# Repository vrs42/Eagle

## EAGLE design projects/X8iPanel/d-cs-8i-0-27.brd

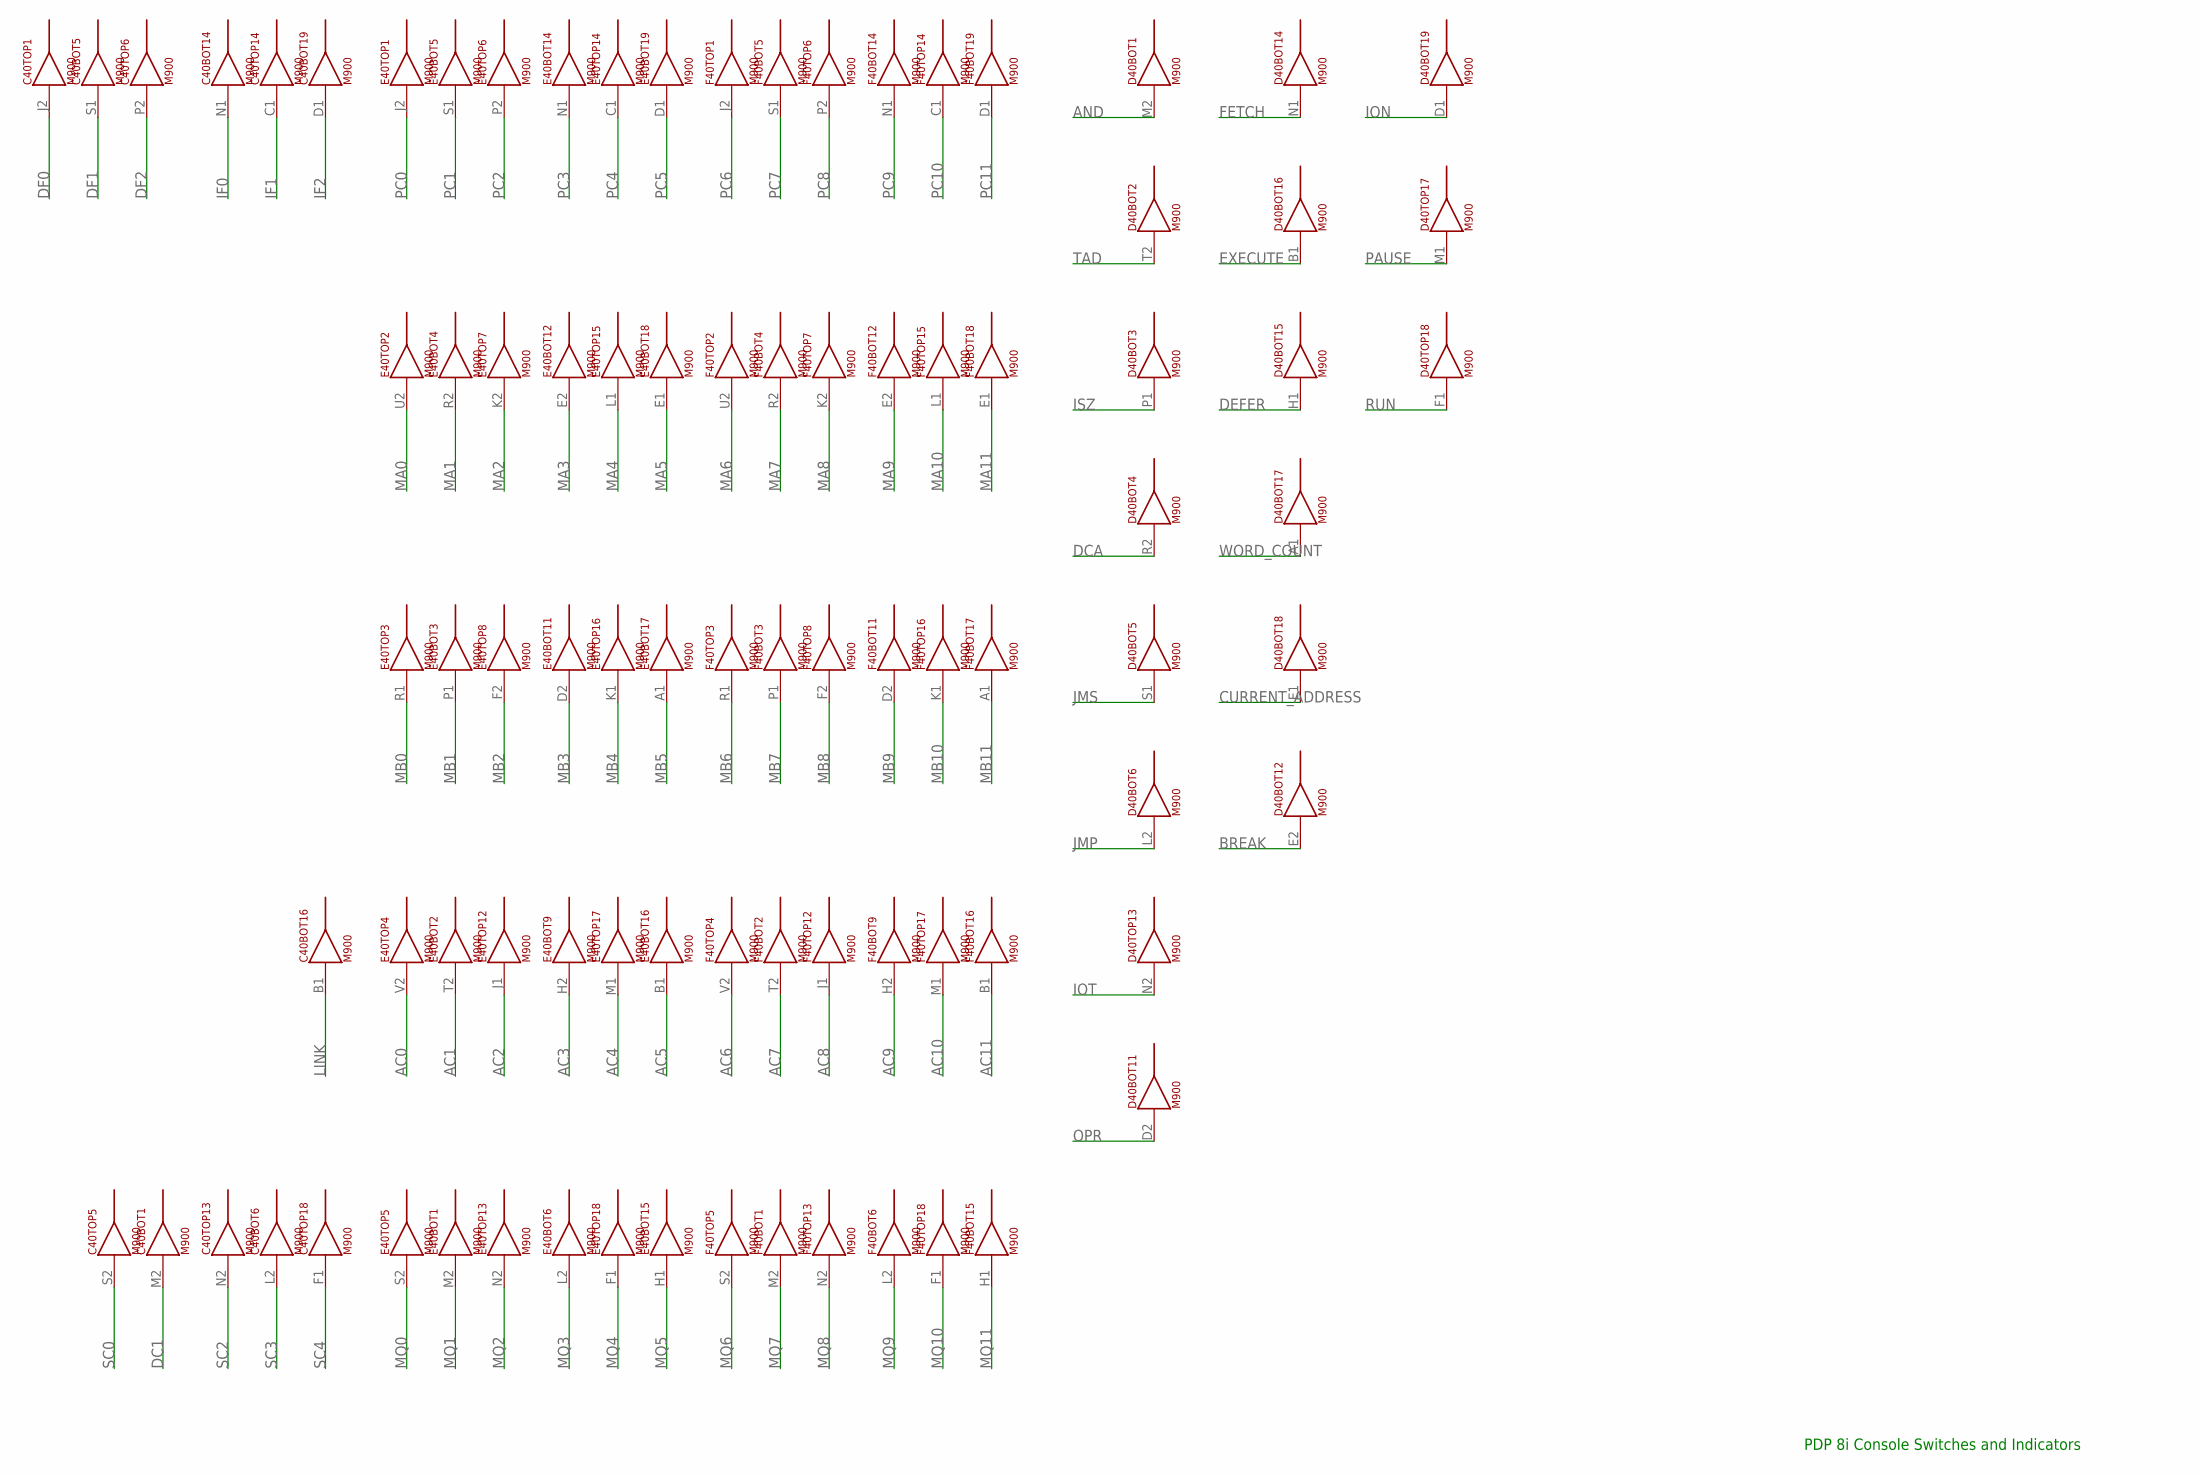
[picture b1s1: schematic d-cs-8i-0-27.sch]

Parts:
C40: M900; H807
D40: M900; H807
E40: M900; H807
F40: M900; H807

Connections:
AC0: E40.V2 (1)
AC1: E40.T2 (1)
AC2: E40.J1 (1)
AC3: E40.H2 (1)
AC4: E40.M1 (1)
AC5: E40.B1 (1)
AC6: F40.V2 (1)
AC7: F40.T2 (1)
AC8: F40.J1 (1)
AC9: F40.H2 (1)
AC10: F40.M1 (1)
AC11: F40.B1 (1)
AND: D40.M2 (1)
BREAK: D40.E2 (1)
CURRENT_ADDRESS: D40.E1 (1)
DC1: C40.M2 (1)
DCA: D40.R2 (1)
DEFER: D40.H1 (1)
DF0: C40.J2 (1)
DF1: C40.S1 (1)
DF2: C40.P2 (1)
EXECUTE: D40.B1 (1)
FETCH: D40.N1 (1)
GND: C40.C2 (GND), C40.T1 (GND), D40.C2 (GND), D40.T1 (GND), E40.C2 (GND), E40.T1 (GND), F40.C2 (GND), F40.T1 (GND)
IF0: C40.N1 (1)
IF1: C40.C1 (1)
IF2: C40.D1 (1)
ION: D40.D1 (1)
IOT: D40.N2 (1)
ISZ: D40.P1 (1)
JMP: D40.L2 (1)
JMS: D40.S1 (1)
LINK: C40.B1 (1)
MA0: E40.U2 (1)
MA1: E40.R2 (1)
MA2: E40.K2 (1)
MA3: E40.E2 (1)
MA4: E40.L1 (1)
MA5: E40.E1 (1)
MA6: F40.U2 (1)
MA7: F40.R2 (1)
MA8: F40.K2 (1)
MA9: F40.E2 (1)
MA10: F40.L1 (1)
MA11: F40.E1 (1)
MB0: E40.R1 (1)
MB1: E40.P1 (1)
MB2: E40.F2 (1)
MB3: E40.D2 (1)
MB4: E40.K1 (1)
MB5: E40.A1 (1)
MB6: F40.R1 (1)
MB7: F40.P1 (1)
MB8: F40.F2 (1)
MB9: F40.D2 (1)
MB10: F40.K1 (1)
MB11: F40.A1 (1)
MQ0: E40.S2 (1)
MQ1: E40.M2 (1)
MQ2: E40.N2 (1)
MQ3: E40.L2 (1)
MQ4: E40.F1 (1)
MQ5: E40.H1 (1)
MQ6: F40.S2 (1)
MQ7: F40.M2 (1)
MQ8: F40.N2 (1)
MQ9: F40.L2 (1)
MQ10: F40.F1 (1)
MQ11: F40.H1 (1)
OPR: D40.D2 (1)
PAUSE: D40.M1 (1)
PC0: E40.J2 (1)
PC1: E40.S1 (1)
PC2: E40.P2 (1)
PC3: E40.N1 (1)
PC4: E40.C1 (1)
PC5: E40.D1 (1)
PC6: F40.J2 (1)
PC7: F40.S1 (1)
PC8: F40.P2 (1)
PC9: F40.N1 (1)
PC10: F40.C1 (1)
PC11: F40.D1 (1)
RUN: D40.F1 (1)
SC0: C40.S2 (1)
SC2: C40.N2 (1)
SC3: C40.L2 (1)
SC4: C40.F1 (1)
TAD: D40.T2 (1)
VCC: C40.A2 (VCC), D40.A2 (VCC), E40.A2 (VCC), F40.A2 (VCC)
WORD_COUNT: D40.A1 (1)

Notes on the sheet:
PDP 8i Console Switches and Indicators

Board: 2 copper layers, 4 parts (0 on the bottom side), 2 nets, no tracks yet.

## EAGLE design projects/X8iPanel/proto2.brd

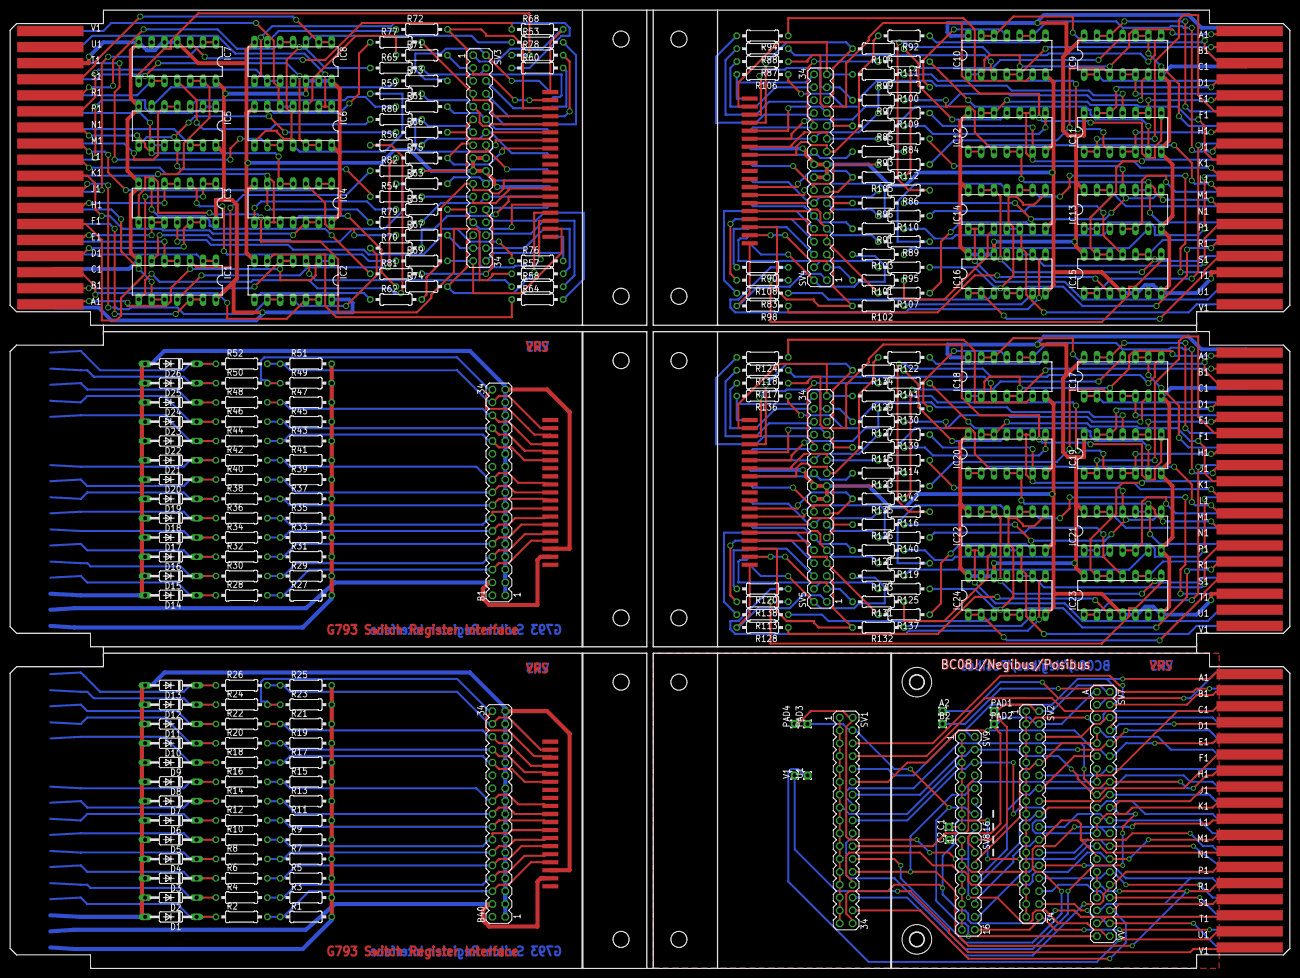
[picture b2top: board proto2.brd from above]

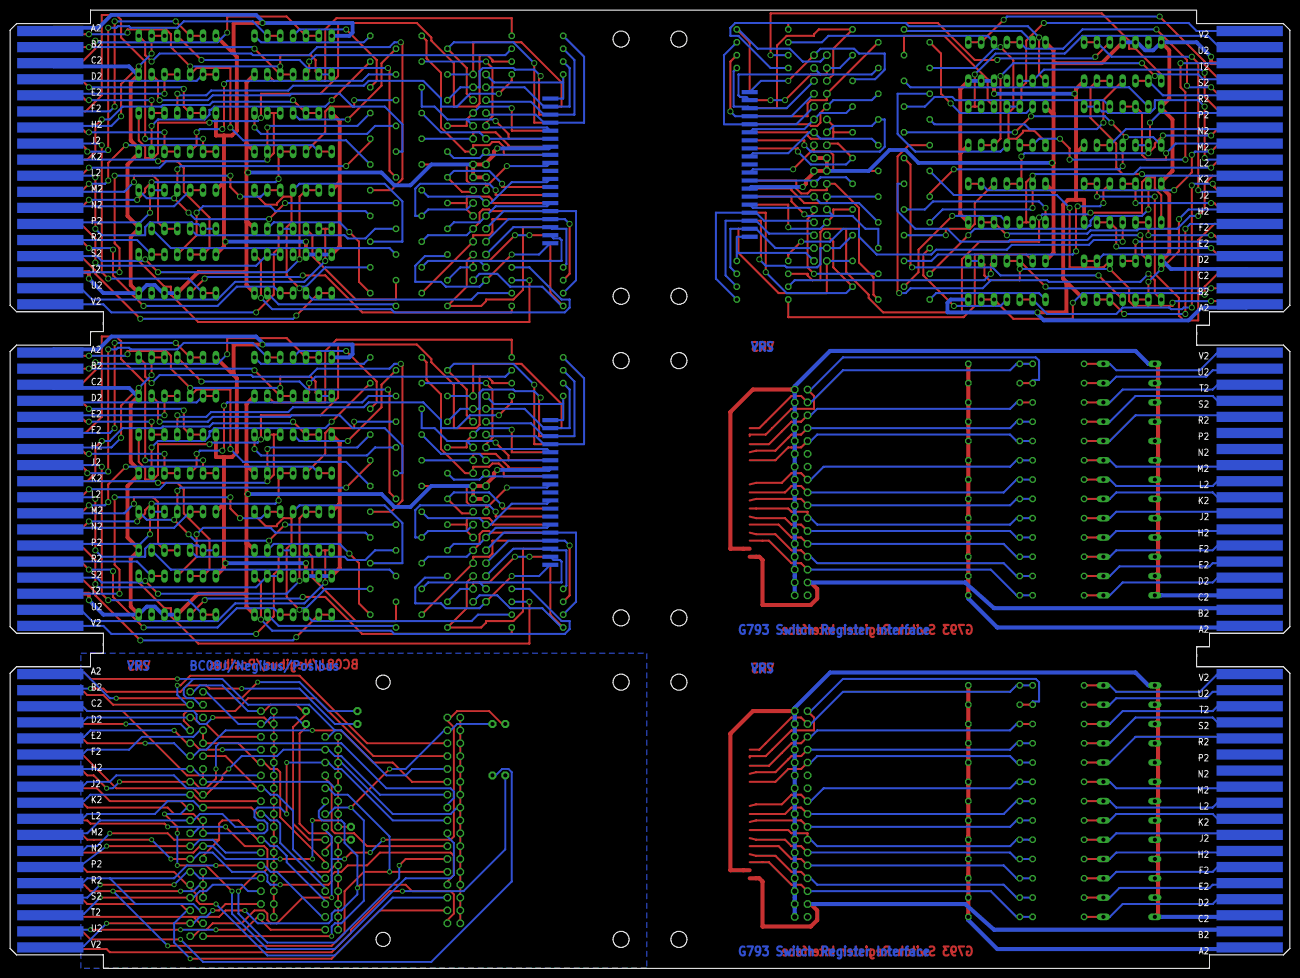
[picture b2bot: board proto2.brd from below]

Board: 2 copper layers, 252.7 x 189.2 mm, 228 parts (3 on the bottom side), 374 nets.

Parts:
A2: 1,6/0,8
B1, B40: MA17-2
B2: 1,6/0,8
BOT, BOT1, BOT2: FLEX19
C1, C2: 1,6/0,8
D1, D2, D3, D4, D5, D6, D7, D8, D9, D10, D11, D12, D13, D14, D15, D16, D17, D18, D19, D20, D21, D22, D23, D24, D25, D26: 1N3606; DO35-10
EDGE, EDGE1, EDGE2: EDGE-CON2
FLEX1, FLEX2: FLEX19
IC1, IC2, IC3, IC4, IC5, IC6, IC7, IC8, IC9, IC10, IC11, IC12, IC13, IC14, IC15, IC16, IC17, IC18, IC19, IC20, IC21, IC22, IC23, IC24: 7400N; DIL14
PAD1, PAD2, PAD3, PAD4: 1,6/0,8
R1, R2, R3, R4, R5, R6, R7, R8, R9, R10, R11, R12, R13, R14, R15, R16, R17, R18, R19, R20, R21, R22, R23, R24, R25, R26, R27, R28, R29, R30, R31, R32, R33, R34, R35, R36, R37, R38, R39, R40, R41, R42, R43, R44, R45, R46, R47, R48, R49, R50, R51, R52: 1.5K; 0207/10
R53, R54, R55, R56, R57, R58, R59, R60, R61, R62, R63, R64, R65, R66, R67, R68, R69, R70, R71, R72, R73, R74, R75, R76, R77, R78, R79, R80, R81, R82, R83, R84, R85, R86, R87, R88, R89, R90, R91, R92, R93, R94, R95, R96, R97, R98, R99, R100, R101, R102, R103, R104, R105, R106, R107, R108, R109, R110, R111, R112, R113, R114, R115, R116, R117, R118, R119, R120, R121, R122, R123, R124, R125, R126, R127, R128, R129, R130, R131, R132, R133, R134, R135, R136, R137, R138, R139, R140, R141, R142: 470; 0207/10
SV1, SV2, SV3, SV4, SV5: MA17-2
SV7: DEC40PINV
SV8, SV9: MA08-2
TOP, TOP1, TOP2: FLEX19
U1: 1,6/0,8
U$2, U$7: EDGE-1; EDGE-CON1
U$9: EDGE-CON2
U$11, U$12: 2,8
V1: 1,6/0,8

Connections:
-15V: B40.4, FLEX1.2, U$2.B2
-15V1: B1.4, FLEX2.2, U$7.B2
-15V2: B2.1, U$9.B2
A1: SV1.10, SV7.C, SV9.2, U$9.A1
B1: SV1.6, SV7.D, U$9.B1
BOT1: BOT.1, R73.2, SV3.2
BOT2: BOT.2, R65.2, SV3.4
BOT3: BOT.3, R60.2, SV3.6
BOT4: BOT.4, R78.2, SV3.8
BOT5: BOT.5, R53.2, SV3.10
BOT6: BOT.6, R61.2, SV3.12
BOT7: BOT1.15, R111.2, SV4.26
BOT8: BOT1.3, R90.2, SV4.6
BOT9: BOT.9, R56.2, SV3.14
BOT10: BOT1.1, R103.2, SV4.2
BOT11: BOT.11, R82.2, SV3.16
BOT12: BOT.12, R63.2, SV3.22
BOT13: BOT1.2, R95.2, SV4.4
BOT14: BOT.14, R79.2, SV3.24
BOT15: BOT.15, R81.2, SV3.26
BOT16: BOT.16, R64.2, SV3.28
BOT17: BOT.17, R58.2, SV3.30
BOT18: BOT.18, R57.2, SV3.32
BOT19: BOT.19, R76.2, SV3.34
BOT20: BOT1.4, R108.2, SV4.8
BOT21: BOT1.5, R83.2, SV4.10
BOT22: BOT1.19, R106.2, SV4.34
BOT23: BOT1.18, R87.2, SV4.32
BOT24: BOT1.17, R88.2, SV4.30
BOT25: BOT1.16, R94.2, SV4.28
BOT26: BOT1.14, R109.2, SV4.24
BOT27: BOT1.12, R93.2, SV4.22
BOT28: BOT1.11, R112.2, SV4.16
BOT29: BOT1.9, R86.2, SV4.14
BOT30: BOT1.6, R91.2, SV4.12
BOT31: BOT2.15, R141.2, SV5.26
BOT32: BOT2.3, R120.2, SV5.6
BOT33: BOT2.1, R133.2, SV5.2
BOT34: BOT2.2, R125.2, SV5.4
BOT35: BOT2.4, R138.2, SV5.8
BOT36: BOT2.5, R113.2, SV5.10
BOT37: BOT2.19, R136.2, SV5.34
BOT38: BOT2.18, R117.2, SV5.32
BOT39: BOT2.17, R118.2, SV5.30
BOT40: BOT2.16, R124.2, SV5.28
BOT41: BOT2.14, R139.2, SV5.24
BOT42: BOT2.12, R123.2, SV5.22
BOT43: BOT2.11, R142.2, SV5.16
BOT44: BOT2.9, R116.2, SV5.14
BOT45: BOT2.6, R121.2, SV5.12
C1: C1.1, SV1.1, SV1.3, SV1.5, SV1.7, SV1.9, SV1.11, SV1.13, SV1.15, SV1.17, SV1.19, SV1.21, SV1.23, SV1.25, SV1.27, SV1.29, SV1.31, SV1.33, SV7.P, SV7.S, SV9.1, SV9.3, SV9.5, SV9.7, SV9.9, SV9.11, SV9.13, SV9.15, U$9.C1
C2: C2.1, SV2.1, SV2.3, SV2.5, SV2.7, SV2.9, SV2.11, SV2.13, SV2.15, SV2.17, SV2.19, SV2.21, SV2.23, SV2.25, SV2.27, SV2.29, SV2.31, SV2.33, SV7.E, SV8.1, SV8.3, SV8.5, SV8.7, SV8.9, SV8.11, SV8.13, SV8.15, U$9.C2
D1: D14.C, R28.1, U$7.D2
D2: D1.C, R2.1, U$2.D2
D3: SV2.6, SV7.F, U$9.D2
D4: SV1.8, SV7.J, U$9.D1
E1: D15.C, R30.1, U$7.E2
E2: D2.C, R4.1, U$2.E2
E3: SV2.8, SV7.L, U$9.E2
E4: SV1.12, SV7.N, U$9.E1
F1: D16.C, R32.1, U$7.F2
F2: D3.C, R6.1, U$2.F2
F3: SV2.10, SV7.H, SV7.K, SV8.6, U$9.F2
F4: SV1.14, SV7.U, SV9.4, U$9.F1
GND2: BOT.13, EDGE.C2, EDGE.T1, IC1.7, IC2.7, IC3.7, IC4.7, IC5.7, IC6.7, IC7.4, IC7.5, IC7.7, IC8.7, SV3.17, SV3.18, SV3.19, SV3.20
GND3: BOT1.13, EDGE1.C2, EDGE1.T1, IC9.7, IC10.7, IC11.7, IC12.7, IC13.7, IC14.7, IC15.4, IC15.5, IC15.7, IC16.7, SV4.17, SV4.18, SV4.19, SV4.20
GND4: BOT2.13, EDGE2.C2, EDGE2.T1, IC17.7, IC18.7, IC19.7, IC20.7, IC21.7, IC22.7, IC23.4, IC23.5, IC23.7, IC24.7, SV5.17, SV5.18, SV5.19, SV5.20
GND5: B40.1, B40.3, B40.5, B40.7, B40.9, B40.11, B40.13, B40.15, B40.17, B40.19, B40.21, B40.23, B40.25, B40.27, B40.29, B40.31, B40.33, D1.A, D2.A, D3.A, D4.A, D5.A, D6.A, D7.A, D8.A, D9.A, D10.A, D11.A, D12.A, D13.A, FLEX1.3, U$2.C2
GND6: B1.1, B1.3, B1.5, B1.7, B1.9, B1.11, B1.13, B1.15, B1.17, B1.19, B1.21, B1.23, B1.25, B1.27, B1.29, B1.31, B1.33, D14.A, D15.A, D16.A, D17.A, D18.A, D19.A, D20.A, D21.A, D22.A, D23.A, D24.A, D25.A, D26.A, FLEX2.3, U$7.C2
H1: D17.C, R34.1, U$7.H2
H2: D4.C, R8.1, U$2.H2
H3: SV2.12, SV7.R, U$9.H2
H4: SV1.16, SV7.T, U$9.H1
J1: D18.C, R36.1, U$7.J2
J2: D5.C, R10.1, U$2.J2
J3: SV1.20, SV7.X, U$9.J1
J4: SV2.14, SV7.M, SV8.8, U$9.J2
JA2: PAD1.1, SV2.2, SV7.B, SV8.2
JB2: PAD2.1, SV2.4, SV7.A, SV8.4
JU1: PAD3.1, SV1.4, SV7.UU, SV9.14
JV1: PAD4.1, SV1.2, SV7.VV, SV9.16
K1: D19.C, R38.1, U$7.K2
K2: D6.C, R12.1, U$2.K2
K3: SV2.16, SV7.V, U$9.K2
K4: SV1.18, SV7.AA, SV7.Y, SV9.6, U$9.K1
L1: D20.C, R40.1, U$7.L2
L2: D7.C, R14.1, U$2.L2
L3: SV1.24, SV7.BB, U$9.L1
L4: SV2.18, SV7.W, SV8.10, U$9.L2
M1: D21.C, R42.1, U$7.M2
M2: D8.C, R16.1, U$2.M2
M3: SV2.20, SV7.Z, U$9.M2
M4: SV1.28, SV7.FF, U$9.M1
N1: SV1.22, SV7.CC, SV9.8, U$9.N1
N2: SV2.22, SV7.EE, SV8.12, U$9.N2
unnamed: EDGE.A1, IC2.1, IC2.2
unnamed: IC2.3, R58.1
unnamed: IC3.8, R57.1
unnamed: IC1.8, R56.1
unnamed: IC4.8, R55.1
unnamed: IC5.11, R54.1
unnamed: EDGE.H2, IC1.9, IC1.10
unnamed: EDGE.S1, IC8.1, IC8.2
unnamed: EDGE.N2, IC5.12, IC5.13
unnamed: EDGE.L1, IC4.9, IC4.10
unnamed: EDGE.E1, IC3.9, IC3.10
unnamed: EDGE.P1, IC8.9, IC8.10
unnamed: EDGE.B1, IC2.4, IC2.5
unnamed: EDGE.E2, IC1.4, IC1.5
unnamed: EDGE.J1, IC2.9, IC2.10
unnamed: EDGE.L2, IC5.1, IC5.2
unnamed: EDGE.S2, IC6.12, IC6.13
unnamed: IC8.8, R60.1
unnamed: IC5.3, R61.1
unnamed: IC2.8, R62.1
unnamed: IC1.6, R63.1
unnamed: IC2.6, R64.1
unnamed: IC6.11, R59.1
unnamed: IC8.3, R53.1
unnamed: EDGE.P2, IC5.9, IC5.10
unnamed: EDGE.C1, IC2.12, IC2.13
unnamed: EDGE.F1, IC3.1, IC3.2
unnamed: EDGE.J2, IC7.1, IC7.2
unnamed: EDGE.M1, IC4.1, IC4.2
unnamed: EDGE.T2, IC6.9, IC6.10
unnamed: IC6.8, R65.1
unnamed: IC5.8, R66.1
unnamed: IC4.3, R67.1
unnamed: IC7.3, R68.1
unnamed: IC2.11, R70.1
unnamed: IC3.3, R69.1
unnamed: IC6.3, R71.1
unnamed: IC8.6, R72.1
unnamed: IC5.6, R73.1
unnamed: IC4.11, R74.1
unnamed: IC1.11, R75.1
unnamed: IC3.11, R76.1
unnamed: EDGE.R1, IC8.4, IC8.5
unnamed: EDGE.F2, IC1.12, IC1.13
unnamed: EDGE.K1, IC4.12, IC4.13
unnamed: EDGE.M2, IC5.4, IC5.5
unnamed: EDGE.U2, IC6.1, IC6.2
unnamed: EDGE.R2, IC7.9, IC7.10
unnamed: EDGE.D1, IC3.12, IC3.13
unnamed: EDGE.D2, IC1.1, IC1.2
unnamed: EDGE.H1, IC3.4, IC3.5
unnamed: EDGE.K2, IC7.12, IC7.13
unnamed: EDGE.N1, IC4.4, IC4.5
unnamed: EDGE.V2, IC6.4, IC6.5
unnamed: IC6.6, R77.1
unnamed: IC7.8, R78.1
unnamed: IC4.6, R79.1
unnamed: IC7.11, R80.1
unnamed: IC3.6, R81.1
unnamed: IC1.3, R82.1
unnamed: EDGE1.A1, IC10.1, IC10.2
unnamed: IC10.3, R88.1
unnamed: IC11.8, R87.1
unnamed: IC9.8, R86.1
unnamed: IC12.8, R85.1
unnamed: IC13.11, R84.1
unnamed: EDGE1.H2, IC9.9, IC9.10
unnamed: EDGE1.S1, IC16.1, IC16.2
unnamed: EDGE1.N2, IC13.12, IC13.13
unnamed: EDGE1.L1, IC12.9, IC12.10
unnamed: EDGE1.E1, IC11.9, IC11.10
unnamed: EDGE1.P1, IC16.9, IC16.10
unnamed: EDGE1.B1, IC10.4, IC10.5
unnamed: EDGE1.E2, IC9.4, IC9.5
unnamed: EDGE1.J1, IC10.9, IC10.10
unnamed: EDGE1.L2, IC13.1, IC13.2
unnamed: EDGE1.S2, IC14.12, IC14.13
unnamed: IC16.8, R90.1
unnamed: IC13.3, R91.1
unnamed: IC10.8, R92.1
unnamed: IC9.6, R93.1
unnamed: IC10.6, R94.1
unnamed: IC14.11, R89.1
unnamed: IC16.3, R83.1
unnamed: EDGE1.P2, IC13.9, IC13.10
unnamed: EDGE1.C1, IC10.12, IC10.13
unnamed: EDGE1.F1, IC11.1, IC11.2
unnamed: EDGE1.J2, IC15.1, IC15.2
unnamed: EDGE1.M1, IC12.1, IC12.2
unnamed: EDGE1.T2, IC14.9, IC14.10
unnamed: IC14.8, R95.1
unnamed: IC13.8, R96.1
unnamed: IC12.3, R97.1
unnamed: IC15.3, R98.1
unnamed: IC10.11, R100.1
unnamed: IC11.3, R99.1
unnamed: IC14.3, R101.1
unnamed: IC16.6, R102.1
unnamed: IC13.6, R103.1
unnamed: IC12.11, R104.1
unnamed: IC9.11, R105.1
unnamed: IC11.11, R106.1
unnamed: EDGE1.R1, IC16.4, IC16.5
unnamed: EDGE1.F2, IC9.12, IC9.13
unnamed: EDGE1.K1, IC12.12, IC12.13
unnamed: EDGE1.M2, IC13.4, IC13.5
unnamed: EDGE1.U2, IC14.1, IC14.2
unnamed: EDGE1.R2, IC15.9, IC15.10
unnamed: EDGE1.D1, IC11.12, IC11.13
unnamed: EDGE1.D2, IC9.1, IC9.2
unnamed: EDGE1.H1, IC11.4, IC11.5
unnamed: EDGE1.K2, IC15.12, IC15.13
unnamed: EDGE1.N1, IC12.4, IC12.5
unnamed: EDGE1.V2, IC14.4, IC14.5
unnamed: IC14.6, R107.1
unnamed: IC15.8, R108.1
unnamed: IC12.6, R109.1
unnamed: IC15.11, R110.1
unnamed: IC11.6, R111.1
unnamed: IC9.3, R112.1
unnamed: EDGE2.A1, IC18.1, IC18.2
unnamed: IC18.3, R118.1
unnamed: IC19.8, R117.1
unnamed: IC17.8, R116.1
unnamed: IC20.8, R115.1
unnamed: IC21.11, R114.1
unnamed: EDGE2.H2, IC17.9, IC17.10
unnamed: EDGE2.S1, IC24.1, IC24.2
unnamed: EDGE2.N2, IC21.12, IC21.13
unnamed: EDGE2.L1, IC20.9, IC20.10
unnamed: EDGE2.E1, IC19.9, IC19.10
unnamed: EDGE2.P1, IC24.9, IC24.10
unnamed: EDGE2.B1, IC18.4, IC18.5
unnamed: EDGE2.E2, IC17.4, IC17.5
unnamed: EDGE2.J1, IC18.9, IC18.10
unnamed: EDGE2.L2, IC21.1, IC21.2
unnamed: EDGE2.S2, IC22.12, IC22.13
unnamed: IC24.8, R120.1
unnamed: IC21.3, R121.1
unnamed: IC18.8, R122.1
unnamed: IC17.6, R123.1
unnamed: IC18.6, R124.1
unnamed: IC22.11, R119.1
unnamed: IC24.3, R113.1
unnamed: EDGE2.P2, IC21.9, IC21.10
unnamed: EDGE2.C1, IC18.12, IC18.13
unnamed: EDGE2.F1, IC19.1, IC19.2
unnamed: EDGE2.J2, IC23.1, IC23.2
unnamed: EDGE2.M1, IC20.1, IC20.2
unnamed: EDGE2.T2, IC22.9, IC22.10
unnamed: IC22.8, R125.1
unnamed: IC21.8, R126.1
unnamed: IC20.3, R127.1
unnamed: IC23.3, R128.1
unnamed: IC18.11, R130.1
unnamed: IC19.3, R129.1
unnamed: IC22.3, R131.1
unnamed: IC24.6, R132.1
unnamed: IC21.6, R133.1
unnamed: IC20.11, R134.1
unnamed: IC17.11, R135.1
unnamed: IC19.11, R136.1
unnamed: EDGE2.R1, IC24.4, IC24.5
unnamed: EDGE2.F2, IC17.12, IC17.13
unnamed: EDGE2.K1, IC20.12, IC20.13
unnamed: EDGE2.M2, IC21.4, IC21.5
unnamed: EDGE2.U2, IC22.1, IC22.2
unnamed: EDGE2.R2, IC23.9, IC23.10
unnamed: EDGE2.D1, IC19.12, IC19.13
unnamed: EDGE2.D2, IC17.1, IC17.2
unnamed: EDGE2.H1, IC19.4, IC19.5
unnamed: EDGE2.K2, IC23.12, IC23.13
unnamed: EDGE2.N1, IC20.4, IC20.5
unnamed: EDGE2.V2, IC22.4, IC22.5
unnamed: IC22.6, R137.1
unnamed: IC23.8, R138.1
unnamed: IC20.6, R139.1
unnamed: IC23.11, R140.1
unnamed: IC19.6, R141.1
unnamed: IC17.3, R142.1
P1: SV1.30, SV7.LL, U$9.P1
P2: SV2.24, SV7.DD, U$9.P2
R1: D22.C, R44.1, U$7.R2
R2: D9.C, R18.1, U$2.R2
R3: SV2.26, SV7.PP, SV8.14, U$9.R2
R4: SV1.26, SV7.HH, SV7.KK, SV7.MM, SV9.10, U$9.R1
S1: D23.C, R46.1, U$7.S2
S2: D10.C, R20.1, U$2.S2
S3: SV2.28, SV7.JJ, U$9.S2
S4: SV1.32, SV7.RR, U$9.S1
SD3: B40.6, FLEX1.4, R1.1, R2.2
SD4: B1.6, FLEX2.4, R27.1, R28.2
SE3: B40.8, FLEX1.5, R3.1, R4.2
SE4: B1.8, FLEX2.5, R29.1, R30.2
SF3: B40.10, FLEX1.6, R5.1, R6.2
SF4: B1.10, FLEX2.6, R31.1, R32.2
SH3: B40.12, FLEX1.7, R7.1, R8.2
SH4: B1.12, FLEX2.7, R33.1, R34.2
SJ1: B1.14, FLEX2.8, R35.1, R36.2
SJ2: B40.14, FLEX1.8, R9.1, R10.2
SK1: B1.16, FLEX2.9, R37.1, R38.2
SK2: B40.16, FLEX1.9, R11.1, R12.2
SL3: B40.18, FLEX1.10, R13.1, R14.2
SL4: B1.18, FLEX2.10, R39.1, R40.2
SM1: B1.20, FLEX2.11, R41.1, R42.2
SM2: B40.20, FLEX1.11, R15.1, R16.2
SR1: B1.26, FLEX2.14, R43.1, R44.2
SR2: B40.26, FLEX1.14, R17.1, R18.2
SS3: B40.28, FLEX1.15, R19.1, R20.2
SS4: B1.28, FLEX2.15, R45.1, R46.2
ST1: B1.30, FLEX2.16, R47.1, R48.2
ST2: B40.30, FLEX1.16, R21.1, R22.2
SU1: B1.34, FLEX2.17, R49.1, R50.2
SU2: B40.34, FLEX1.17, R23.1, R24.2
SV1: B1.32, FLEX2.18, R51.1, R52.2
SV2: B40.32, FLEX1.18, R25.1, R26.2
T1: D24.C, R48.1, U$7.T2
T2: D11.C, R22.1, U$2.T2
T3: SV2.30, SV7.NN, U$9.T2
T4: SV1.34, SV7.SS, SV9.12, U$9.T1
TOP1: R68.2, SV3.1, TOP.1
TOP2: R71.2, SV3.3, TOP.2
TOP3: R72.2, SV3.5, TOP.3
TOP4: R77.2, SV3.7, TOP.4
TOP5: R59.2, SV3.9, TOP.5
TOP6: R66.2, SV3.11, TOP.6
TOP7: R80.2, SV3.13, TOP.7
TOP8: R75.2, SV3.15, TOP.8
TOP9: R99.2, SV4.33, TOP1.18
TOP10: R97.2, SV4.31, TOP1.17
TOP11: R104.2, SV4.29, TOP1.16
TOP12: R62.2, SV3.21, TOP.12
TOP13: R54.2, SV3.23, TOP.13
TOP14: R70.2, SV3.25, TOP.14
TOP15: R55.2, SV3.27, TOP.15
TOP16: R74.2, SV3.29, TOP.16
TOP17: R67.2, SV3.31, TOP.17
TOP18: R69.2, SV3.33, TOP.18
TOP19: R85.2, SV4.27, TOP1.15
TOP20: R100.2, SV4.25, TOP1.14
TOP21: R84.2, SV4.23, TOP1.13
TOP22: R105.2, SV4.15, TOP1.8
TOP23: R110.2, SV4.13, TOP1.7
TOP24: R96.2, SV4.11, TOP1.6
TOP25: R89.2, SV4.9, TOP1.5
TOP26: R107.2, SV4.7, TOP1.4
TOP27: R98.2, SV4.1, TOP1.1
TOP28: R92.2, SV4.21, TOP1.12
TOP29: R101.2, SV4.3, TOP1.2
TOP30: R102.2, SV4.5, TOP1.3
TOP33: R129.2, SV5.33, TOP2.18
TOP35: R127.2, SV5.31, TOP2.17
TOP38: R134.2, SV5.29, TOP2.16
TOP39: R115.2, SV5.27, TOP2.15
TOP41: R130.2, SV5.25, TOP2.14
TOP42: R114.2, SV5.23, TOP2.13
TOP43: R135.2, SV5.15, TOP2.8
TOP45: R140.2, SV5.13, TOP2.7
TOP46: R126.2, SV5.11, TOP2.6
TOP47: R119.2, SV5.9, TOP2.5
TOP48: R137.2, SV5.7, TOP2.4
TOP49: R128.2, SV5.1, TOP2.1
TOP50: R122.2, SV5.21, TOP2.12
TOP51: R131.2, SV5.3, TOP2.2
TOP52: R132.2, SV5.5, TOP2.3
U1: D25.C, R50.1, U$7.U2
U2: D12.C, R24.1, U$2.U2
U3: U1.1, U$9.U1
U4: SV2.34, SV8.16, U$9.U2
V1: D26.C, R52.1, U$7.V2
V2: D13.C, R26.1, U$2.V2
V3: SV2.32, SV7.TT, U$9.V2
V4: U$9.V1, V1.1
VCC2: R1.2, R3.2, R5.2, R7.2, R9.2, R11.2, R13.2, R15.2, R17.2, R19.2, R21.2, R23.2, R25.2, U$2.A2
VCC3: EDGE.A2, IC1.14, IC2.14, IC3.14, IC4.14, IC5.14, IC6.14, IC7.14, IC8.12, IC8.13, IC8.14
VCC4: R27.2, R29.2, R31.2, R33.2, R35.2, R37.2, R39.2, R41.2, R43.2, R45.2, R47.2, R49.2, R51.2, U$7.A2
VCC6: A2.1, U$9.A2
VCC7: EDGE1.A2, IC9.14, IC10.14, IC11.14, IC12.14, IC13.14, IC14.14, IC15.14, IC16.12, IC16.13, IC16.14
VCC8: EDGE2.A2, IC17.14, IC18.14, IC19.14, IC20.14, IC21.14, IC22.14, IC23.14, IC24.12, IC24.13, IC24.14
